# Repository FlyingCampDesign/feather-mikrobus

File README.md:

# feather-mikrobus
A simple [Adafruit Feather](https://www.adafruit.com/feather) to [mikroBUS](https://www.mikroe.com/mikrobus) socket adapter board.

View this project on [CADLAB.io](https://cadlab.io/project/22579). 

## Hardware

Hardware source files for [KiCad](https://kicad.org) are available in the `hardware/` directory.  For details on features and pinouts, see the individual `README.md` for each hardware version.

### Hacking

The KiCad source files depend on the [Flying Camp Design KiCad Library](https://github.com/FlyingCampDesign/fcd-kicad-lib) being available as a git submodule.  The easiest way to ensure that all dependencies are available is to clone this repository using the following command:

```bash
git clone --recurse-submodules https://github.com/FlyingCampDesign/feather-mikrobus.git
```

To ensure that the 3D model paths are configured correctly for the 3D viewer, make sure to follow the FCD library [usage instructions](https://github.com/FlyingCampDesign/fcd-kicad-lib#usage) (otherwise, none of the 3D models will show up).

### [Feather mikroBUS V1](hardware/feather-mikrobus-v1/)

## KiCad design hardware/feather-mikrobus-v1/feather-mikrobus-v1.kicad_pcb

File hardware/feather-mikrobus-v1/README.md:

# Feather mikroBUS V1

## Features

* Power On/Off switch
* +3.3V power indicator LED
* User button
* User LED
* Bootloader enable (BOOT0) button for [Adafruit Feather STM32F405 Express](https://www.adafruit.com/product/4382)

## Pinout

| Feather Pin Name | mikroBUS Pin Name | FeatherWing Function                                         |
| ---------------- | ----------------- | ------------------------------------------------------------ |
| RESET            |                   | (not used)                                                   |
| 3V3              | +3.3V             | +3.3V                                                        |
| AREF             |                   | Connected to +3.3V via 0Ω jumper R5                          |
| GND              | GND               | GND                                                          |
| A0               | AN                |                                                              |
| A1               |                   | (not used)                                                   |
| A2               |                   | (not used)                                                   |
| A3               |                   | (not used)                                                   |
| A4               |                   | (not used)                                                   |
| A5               |                   | (not used)                                                   |
| SCK              | SCK               |                                                              |
| MOSI             | MOSI              |                                                              |
| MISO             | MISO              |                                                              |
| TX               | RX                |                                                              |
| RX               | TX                |                                                              |
| FREE             |                   | Connected to BOOT0 button SW2 for [Adafruit Feather STM32F405 Express](https://www.adafruit.com/product/4382) |
| SCL              | SCL               |                                                              |
| SDA              | SDA               |                                                              |
| D2               | INT               |                                                              |
| D3               | PWM               |                                                              |
| D4               | RST               |                                                              |
| D5               |                   | Connected to user LED D1 (active low)                        |
| D6               |                   | Connected to user button SW3 (active low)                    |
| D7               | CS                |                                                              |
| D8               |                   | (not used)                                                   |
| VUSB             | +5V               | +5V                                                          |
| EN               |                   | Controlled by SW1                                            |
| VBAT             |                   | (not used)                                                   |

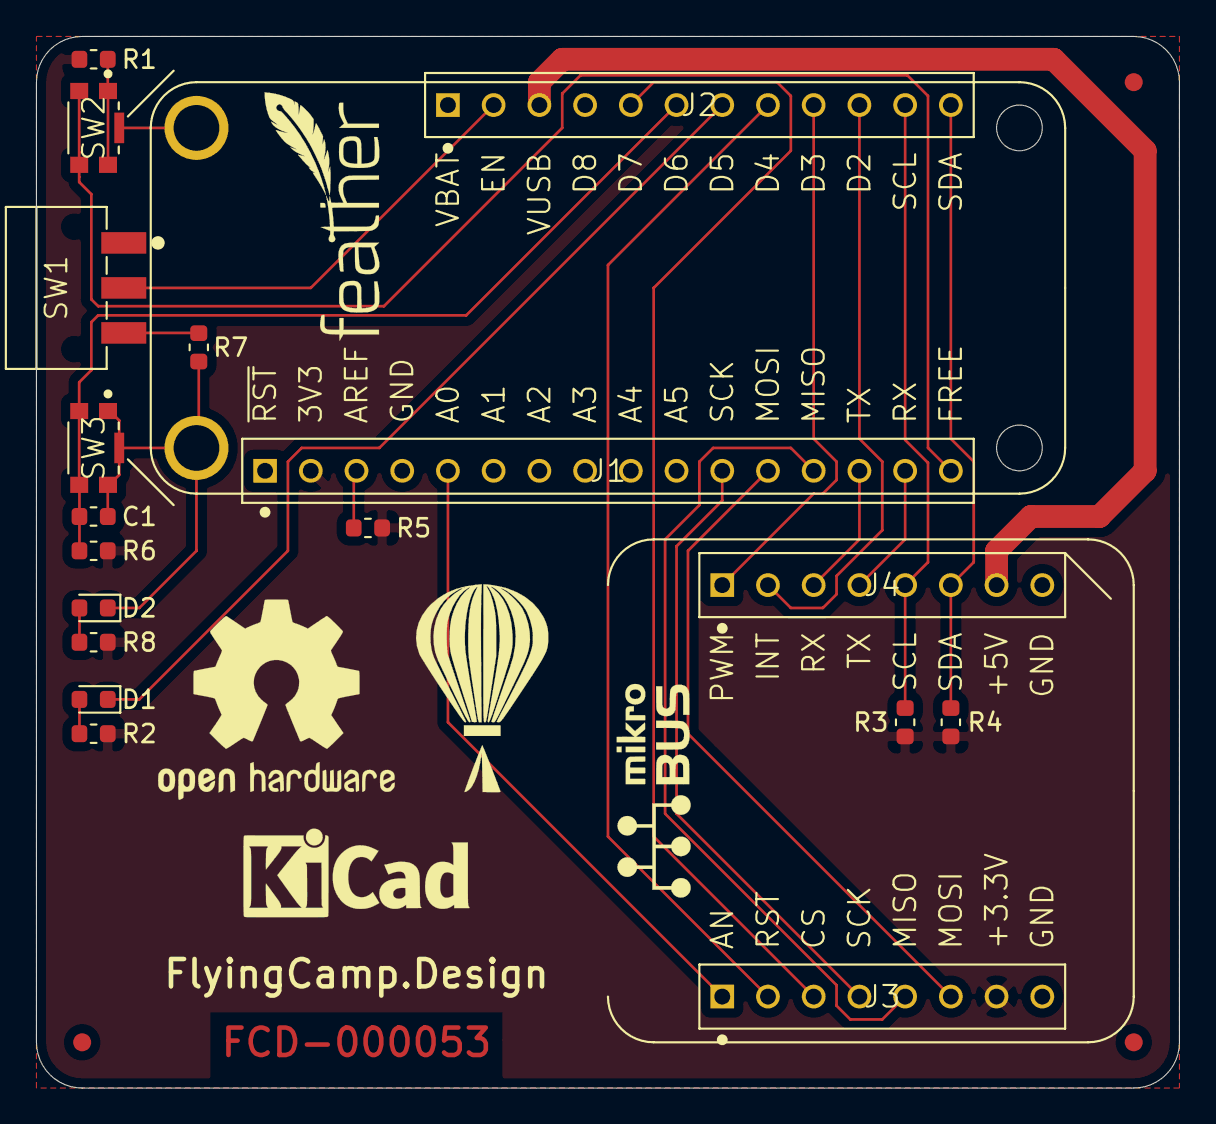
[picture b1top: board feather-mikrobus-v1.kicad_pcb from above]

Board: 2 copper layers, 63.5 x 58.4 mm, 23 parts (0 on the bottom side), 24 nets.

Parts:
C1: Murata_GRM188R72A104KA35D-Flying_Camp_Design; C_0603_1608Metric
D1, D2: Lite-On_LTST-C193KGKT-5A-Flying_Camp_Design; LED_0603_1608Metric
FID1, FID2, FID3: FIDUCIAL_GLOBAL_1X2MM
J1: FCD-000047; TE_6-534237-4
J2: FCD-000048; TE_6-534237-0
J3, J4: FCD-000050; TE_5-534237-6
MOD1: MODULE_ADAFRUIT_FEATHER
MOD2: MODULE_MIKROBUS
R1: Yageo_RC0603JR-071KL-Flying_Camp_Design; R_0603_1608Metric
R2, R8: Yageo_RC0603JR-07330RL-Flying_Camp_Design; R_0603_1608Metric
R3, R4: Yageo_RC0603JR-074K7L-Flying_Camp_Design; R_0603_1608Metric
R5: Yageo_RC0603JR-070RL-Flying_Camp_Design; R_0603_1608Metric
R6: Yageo_RC0603JR-0710KL-Flying_Camp_Design; R_0603_1608Metric
R7: Yageo_RC0603JR-07100RL-Flying_Camp_Design; R_0603_1608Metric
SW1: FCD-000051; CK_JS102011SAQN
SW2, SW3: FCD-000049; CK_KMR4

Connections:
+3V3: J1.2, J3.7, R1.1, R2.1, R3.1, R4.1, R5.1, R6.1, R8.1
+5V: J2.3, J4.7
/3V3_LED_R: D2.2, R8.2
/CS: J2.5, J3.3
/EN_SW_R: R7.1, SW1.3
/FEATHER_AREF: J1.3, R5.2
/FEATHER_EN: J2.2, SW1.2
/FEATHER_FREE: J1.16, SW2.3, SW2.4
/FEATHER_RX: J1.15, J4.4
/FEATHER_TX: J1.14, J4.3
/MIKROBUS_AN: J1.5, J3.1
/MIKROBUS_INT: J2.10, J4.2
/MIKROBUS_PWM: J2.9, J4.1
/MISO: J1.13, J3.5
/MOSI: J1.12, J3.6
/SCK: J1.11, J3.4
/SCL: J2.11, J4.5, R3.2
/SDA: J2.12, J4.6, R4.2
/SW2_R: R1.2, SW2.1, SW2.2
/USER_LED_R: D1.2, R2.2
/~MIKROBUS_RST: J2.8, J3.2
/~USER_LED: D1.1, J2.7
/~USER_SW: C1.1, J2.6, R6.2, SW3.3, SW3.4
GND: C1.2, D2.1, J1.4, J3.8, J4.8, MOD1.MH1, MOD1.MH2, R7.2, SW2.5, SW3.1, SW3.2, SW3.5

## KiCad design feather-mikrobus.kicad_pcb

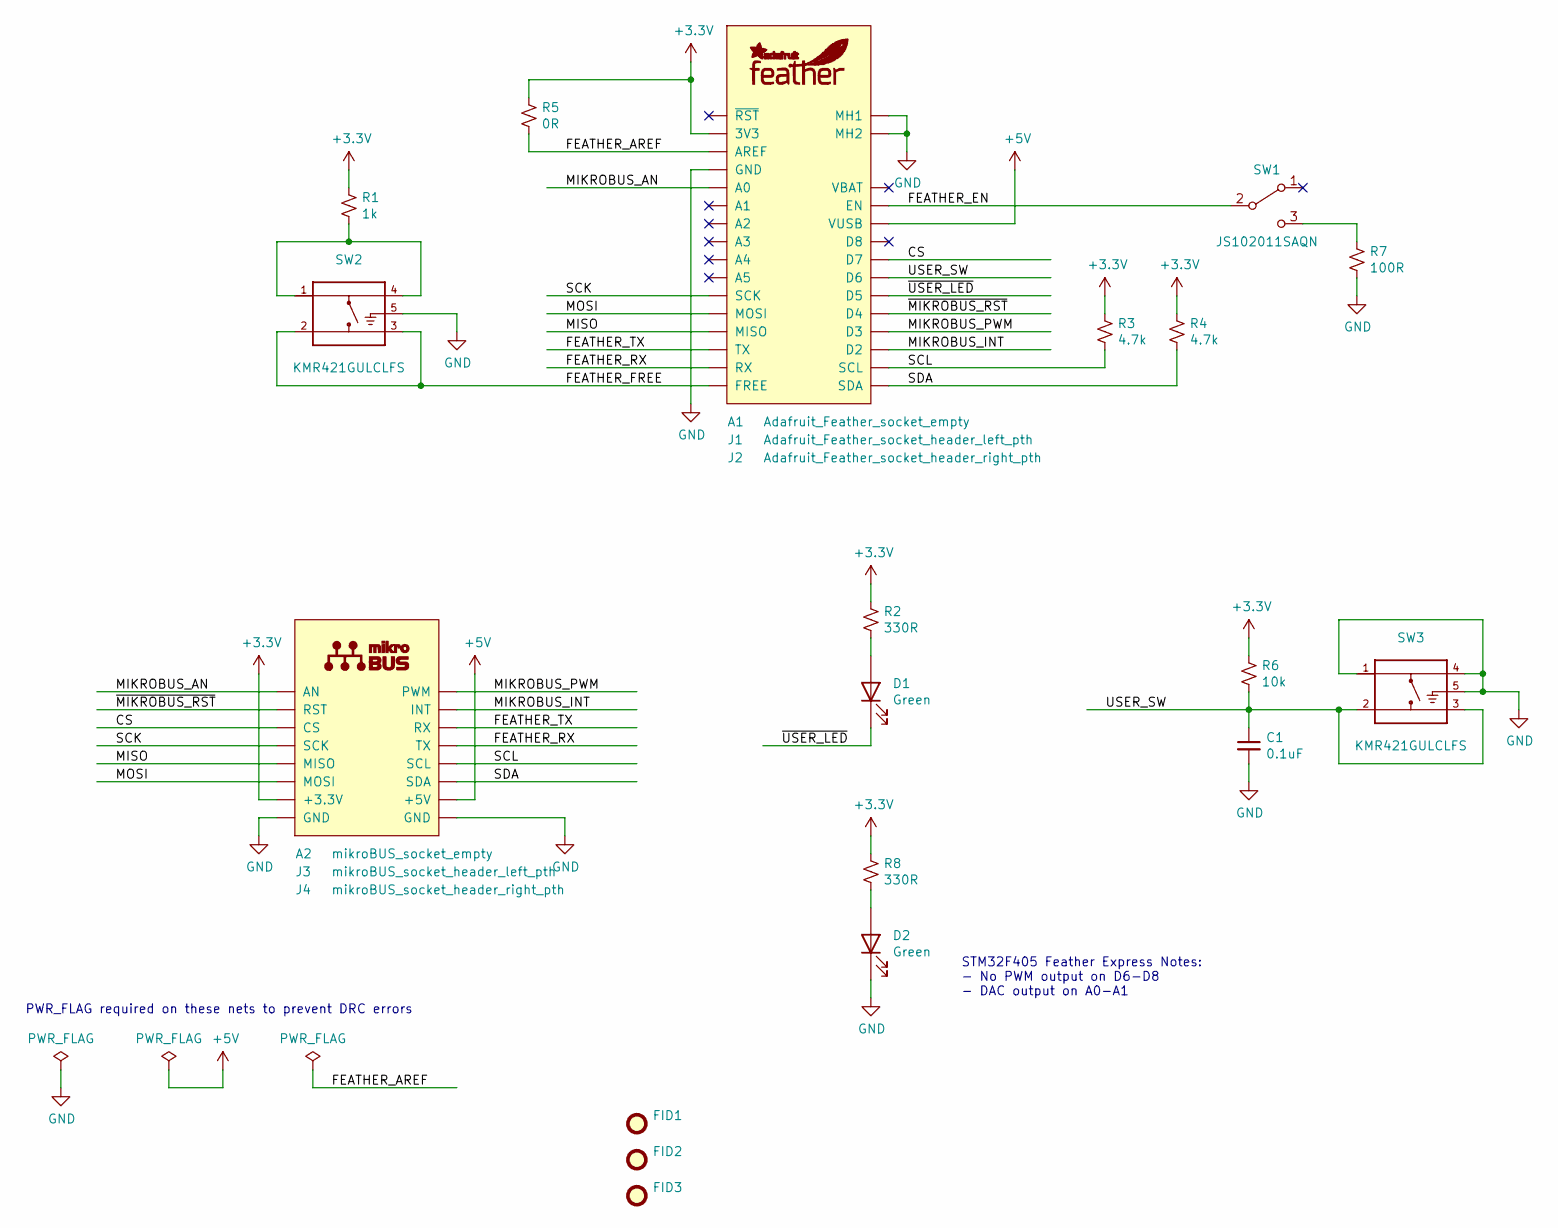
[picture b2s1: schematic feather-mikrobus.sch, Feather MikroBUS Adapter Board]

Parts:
A1: Adafruit_Feather_socket_empty
A2: mikroBUS_socket_empty
C1: GRM188R72A104KA35D; C_0603_1608Metric; Manufacturer Part Number GRM188R72A104KA35D
D1, D2: LTST-C191KGKT; LED_0603_1608Metric; Manufacturer Part Number LTST-C191KGKT
FID1, FID2, FID3: Fiducial_1mm_Mask2mm
J1: Adafruit_Feather_socket_header_left_pth
J2: Adafruit_Feather_socket_header_right_pth
J3: mikroBUS_socket_header_left_pth
J4: mikroBUS_socket_header_right_pth
LOGO1: mikroBUS_logo; mikroBUS-Logo_11.9x4.1mm_SilkScreen
LOGO3: Adafruit_Feather_logo
MH1: Adafruit_Feather_socket_mounting_holes
R1: RC0603JR-071KL; R_0603_1608Metric; Manufacturer Part Number RC0603JR-071KL
R2, R8: RC0603JR-07330RL; R_0603_1608Metric; Manufacturer Part Number RC0603JR-07330RL
R3, R4: RC0603JR-074K7L; R_0603_1608Metric; Manufacturer Part Number RC0603JR-074K7L
R5: RC0603JR-070RL; R_0603_1608Metric; Manufacturer Part Number RC0603JR-070RL
R6: RC0603JR-0710KL; R_0603_1608Metric; Manufacturer Part Number RC0603JR-0710KL
R7: RC0603JR-07100RL; R_0603_1608Metric; Manufacturer Part Number RC0603JR-07100RL
SW1: JS102011SAQN; Manufacturer Part Number JS102011SAQN
SW2, SW3: KMR421GULCLFS; Manufacturer Part Number KMR421GULCLFS

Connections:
+3V3: J1.3V3, J3.+3.3V, R1.1, R2.1, R3.1, R4.1, R5.1, R6.1, R8.1
+5V: J2.VUSB, J4.+5V
/CS: J2.D7, J3.CS
/FEATHER_AREF: J1.AREF, R5.2
/FEATHER_EN: J2.EN, SW1.2 (B)
/FEATHER_FREE: J1.FREE, SW2.2, SW2.3
/FEATHER_RX: J1.RX, J4.TX
/FEATHER_TX: J1.TX, J4.RX
/MIKROBUS_AN: J1.A0, J3.AN
/MIKROBUS_INT: J2.D2, J4.INT
/MIKROBUS_PWM: J2.D3, J4.PWM
/MISO: J1.MISO, J3.MISO
/MOSI: J1.MOSI, J3.MOSI
/SCK: J1.SCK, J3.SCK
/SCL: J2.SCL, J4.SCL, R3.2
/SDA: J2.SDA, J4.SDA, R4.2
/USER_SW: C1.1, J2.D6, R6.2, SW3.2, SW3.3
/~MIKROBUS_RST: J2.D4, J3.RST
/~USER_LED: D1.1 (K), J2.D5
GND: C1.2, D2.1 (K), J1.GND, J3.GND, J4.GND, MH1.MH1, MH1.MH2, R7.2, SW2.5 (G), SW3.1, SW3.4, SW3.5 (G)
unnamed: D1.2 (A), R2.2
unnamed: D2.2 (A), R8.2
unnamed: R1.2, SW2.1, SW2.4
unnamed: R7.1, SW1.3 (C)

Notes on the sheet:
STM32F405 Feather Express Notes: - No PWM output on D6-D8 - DAC output on A0-A1
PWR_FLAG required on these nets to prevent DRC errors

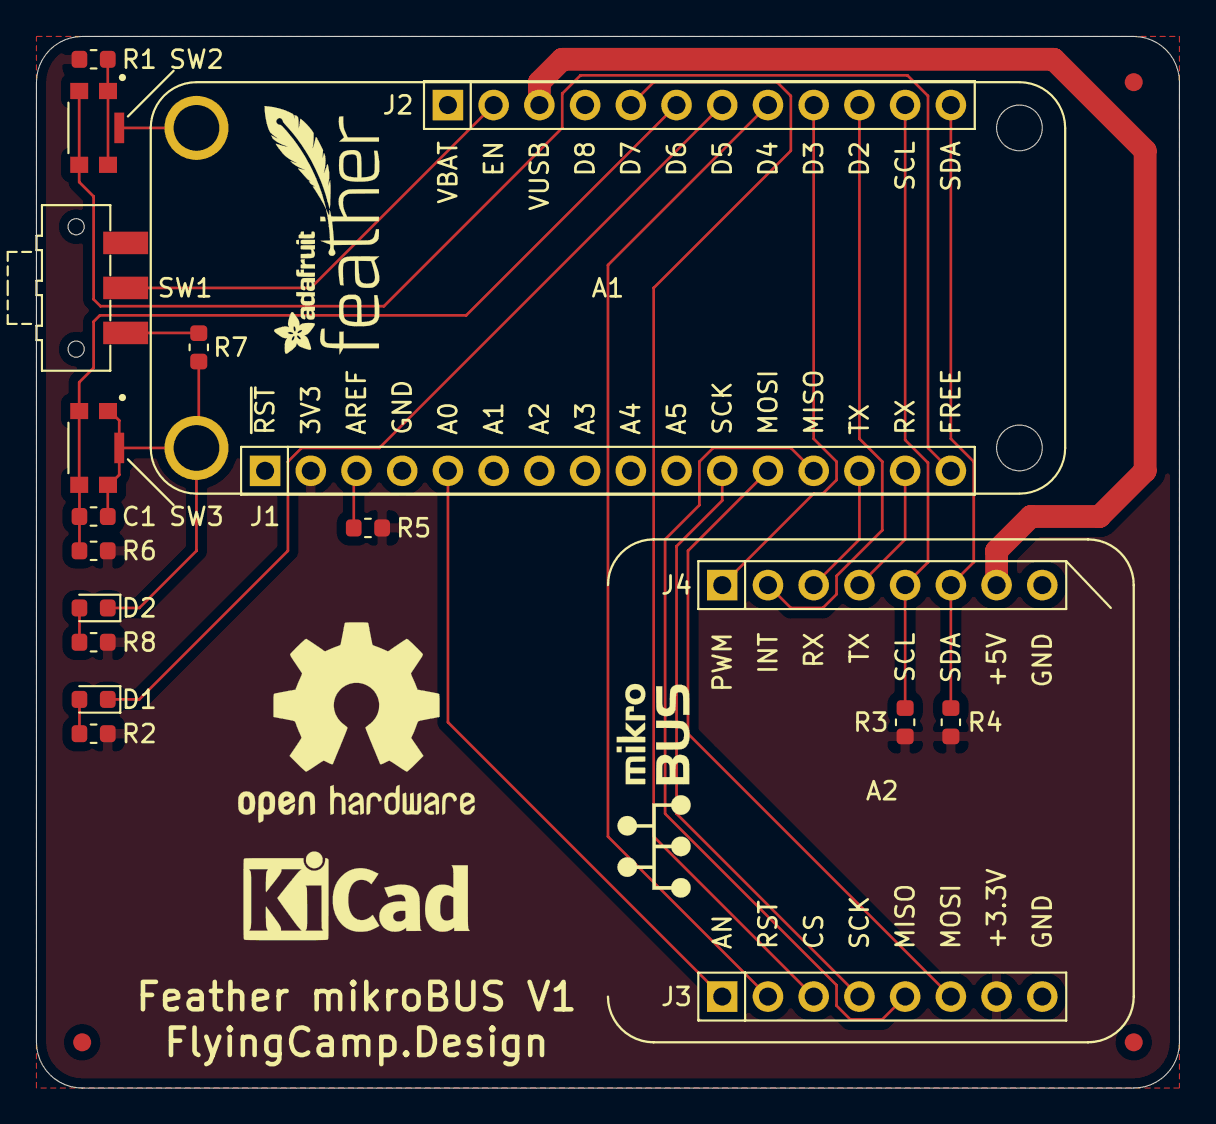
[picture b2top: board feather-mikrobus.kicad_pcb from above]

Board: 2 copper layers, 63.5 x 58.4 mm, 26 parts (0 on the bottom side), 24 nets.

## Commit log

2020-02-10 WIP: add initial design files
2020-02-11 Change names
2020-02-12 Finish schematic and board routing for V1
2020-02-12 Minor cosmetic updates to drawings
2020-02-12 Ignore plots/ dir
2020-02-12 Move KiCad design into hardware subdirectory
2020-02-12 Add version to KiCad file names
2020-02-12 Add version to drawing frame title
2020-02-12 Fix license copyright
2020-02-24 Update symbols and minor cleanup
2020-03-08 Update fcd-kicad-lib submodule
2020-03-08 Remove dependencies on KISYS3DMOD
2020-03-08 Clean up PCB file
2020-03-10 Add hardware README file for V1
2020-03-10 Fix typo in README
2020-03-10 Link to version directory instead of README
2020-03-10 Add hacking instructions to README
2020-03-10 Add pinout to V1 README
2020-03-10 Update V1 README
2020-03-10 Fix title of V1 README
2020-03-10 Fix typo in V1 README
2020-03-10 Update schematic with finalized manufacturers and vendors
2020-03-10 Import latest netlist into PCB
2020-03-10 Backlink to CADLAB.io has been added.
2020-03-10 Make V1 image square
2020-03-10 Update sheet fields
2020-03-11 Update schematic to use new symbols and worksheet
2020-03-11 Add Flying Camp Design logo
2020-03-11 Add Flying Camp Design logos
2020-03-11 Remove dependencies on global libraries
2020-03-11 Update V1 image
2020-03-14 Change LICENSE to CERN-OHL-P
2020-03-14 Move LICENSE into V1 dir
2021-02-27 Upgrade design to KiCad 5.99
2021-03-01 Update design to KiCad 6 formats
2021-03-01 Remove Adafruit star from Feather logo
2021-03-01 Update KiCad URL
2021-06-14 Revert "Update KiCad URL"
    This reverts commit 2d5a2093c9c00809c1c9f870612bf2622a1c6c3e.
2021-06-14 Revert "Remove Adafruit star from Feather logo"
    This reverts commit b8ad0b09bffcc386ca4397281ed953137447e20d.
2021-06-14 Revert "Update design to KiCad 6 formats"
    This reverts commit e90d167ee0dfb78906e166fe0c4b3ad904510116.
2021-06-14 Revert "Upgrade design to KiCad 5.99"
    This reverts commit 404d8fe5192a3f2d218e68c3ca65a2b30fdaee8b.
2021-06-14 Remove Adafruit star from Feather logo in README image
2021-06-15 [WIP] Update logos
2021-06-16 [WIP] Start migration of legacy parts
2021-06-16 [WIP] Update Adafruit Feather legacy footprints
2021-06-17 [WIP] Update legacy mikroBUS symbols

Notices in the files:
hardware/feather-mikrobus-v1/feather-mikrobus-v1.kicad_pcb:
© 2020 Flying Camp Design
Licensed under CERN-OHL-P version 2
